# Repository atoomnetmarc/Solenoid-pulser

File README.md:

# Status

Prototype. Circuit has been validated and know to work on a breadboard, but have not been made into a pcb yet.

# Ding!?

This circuit charges a 2200uF capacitor with a 100 ohm resistor and pulses a 12V JF-0530B solenoid for about 15ms with a NE555 timer chip. The NE555 is configured as a non-retriggerable one-shot timer where the length of the trigger pulse does not matter. The solenoid will strike a reception desk bell to produce a ding sound. The 100 ohm resistor limits triggering to a maximum of once per second. Add a 6mm bushing to the solenoid axle to shorten its throw.

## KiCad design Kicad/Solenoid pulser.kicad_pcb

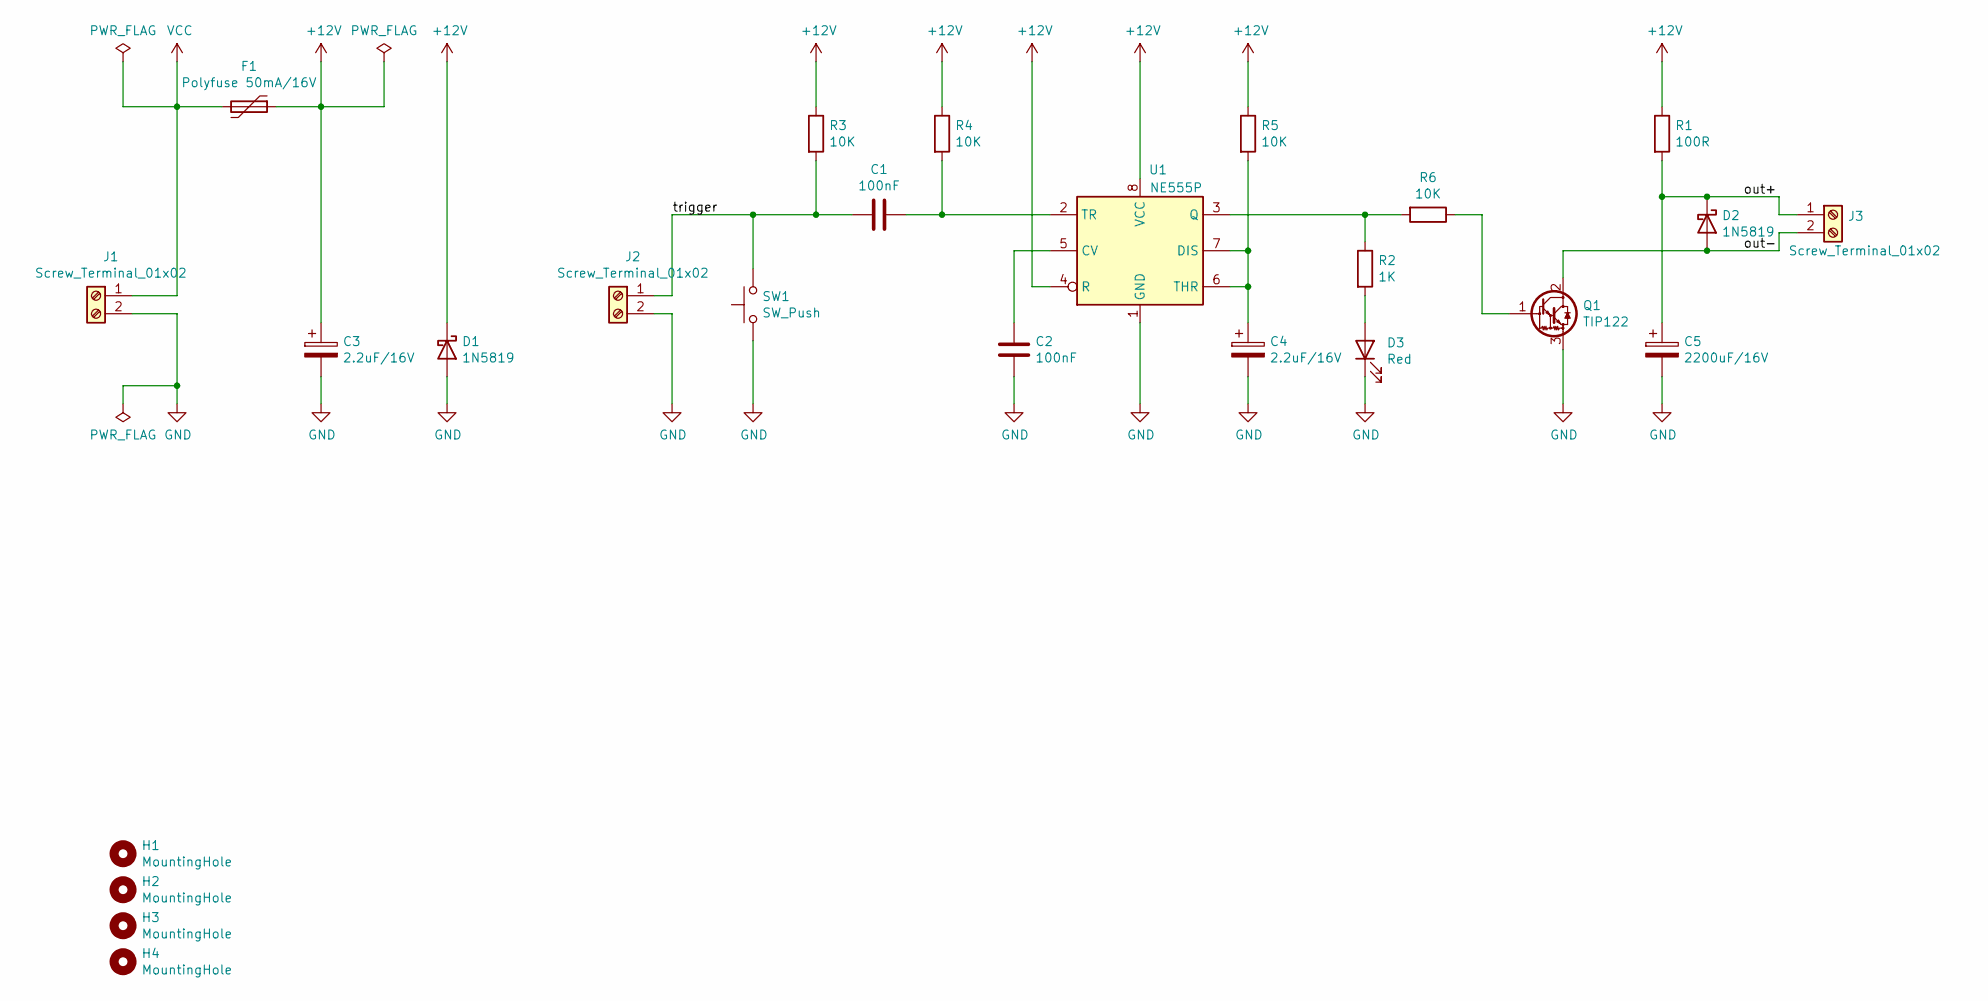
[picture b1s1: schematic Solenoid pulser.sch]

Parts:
C1, C2: 100nF; C_Disc_D5.0mm_W2.5mm_P2.50mm
C3, C4: 2.2uF/16V; CP_Radial_D4.0mm_P2.00mm
C5: 2200uF/16V; CP_Radial_D10.0mm_P5.00mm
D1, D2: 1N5819; D_DO-41_SOD81_P5.08mm_Vertical_KathodeUp
D3: Red; LED_D5.0mm
F1: Polyfuse 50mA/16V; Fuse_Bourns_MF-RG300
H1, H2, H3, H4: MountingHole; MountingHole_3.2mm_M3_Pad_Via
J1, J2, J3: Screw_Terminal_01x02; TerminalBlock_bornier-2_P5.08mm
Q1: TIP122; TO-220-3_Vertical
R1: 100R; R_Axial_DIN0207_L6.3mm_D2.5mm_P5.08mm_Vertical
R2: 1K; R_Axial_DIN0207_L6.3mm_D2.5mm_P5.08mm_Vertical
R3, R4, R5, R6: 10K; R_Axial_DIN0207_L6.3mm_D2.5mm_P5.08mm_Vertical
SW1: SW_Push; SW_PUSH_6mm
U1: NE555P; DIP-8_W7.62mm

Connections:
+12V: C3.1, D1.1 (K), F1.1, R1.1, R3.1, R4.1, R5.1, U1.4 (R), U1.8 (VCC)
/out+: C5.1, D2.1 (K), J3.1, R1.2
/out-: D2.2 (A), J3.2, Q1.2 (C)
/trigger: C1.2, J2.1, R3.2, SW1.2
GND: C2.2, C3.2, C4.2, C5.2, D1.2 (A), D3.1 (K), J1.2, J2.2, Q1.3 (E), SW1.1, U1.1 (GND)
unnamed: C1.1, R4.2, U1.2 (TR)
unnamed: C2.1, U1.5 (CV)
unnamed: C4.1, R5.2, U1.6 (THR), U1.7 (DIS)
unnamed: D3.2 (A), R2.2
unnamed: Q1.1 (B), R6.1
unnamed: R2.1, R6.2, U1.3 (Q)
VCC: F1.2, J1.1

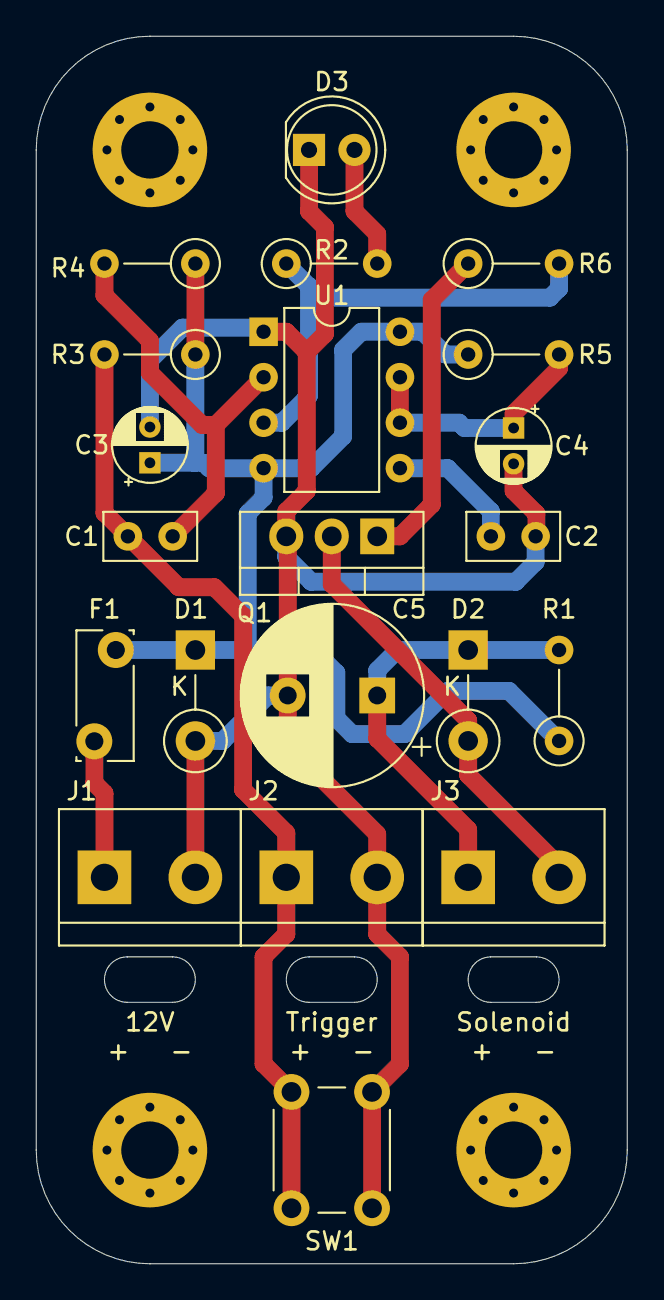
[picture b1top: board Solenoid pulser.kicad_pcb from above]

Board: 2 copper layers, 33.0 x 68.6 mm, 25 parts (0 on the bottom side), 12 nets.

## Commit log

2021-08-06 Initial commit.
2021-09-19 First try 3d design bell holder.
2021-09-19 Added example assembly.
2021-09-20 Tweak pcb and 3d design.
2021-09-21 Generate gerber and BOM.
2021-10-03 Tweak screw hole diameter.
2021-10-03 Tweak spacer hole diameter.

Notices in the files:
Kicad/Solenoid pulser.kicad_pcb:
Apache License, Version 2.0
README.md:
License: Apache 2.0
